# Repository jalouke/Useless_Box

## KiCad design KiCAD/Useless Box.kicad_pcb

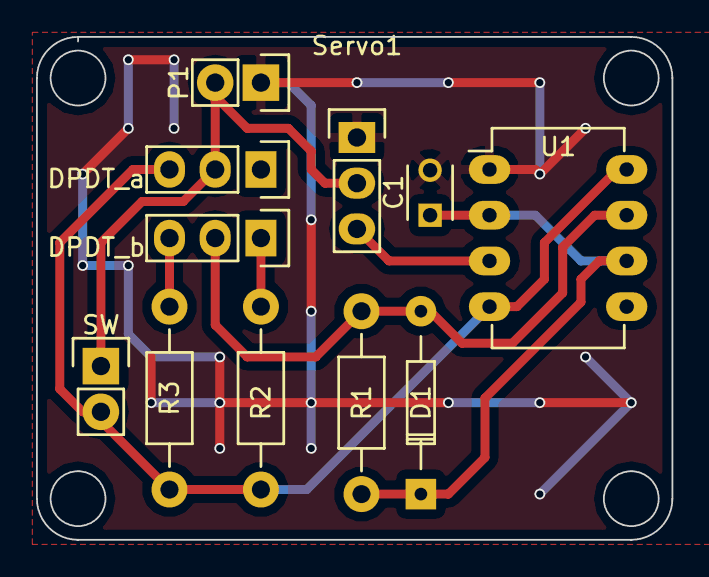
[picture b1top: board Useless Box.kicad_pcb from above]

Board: 2 copper layers, 35.3 x 27.9 mm, 11 parts (0 on the bottom side), 8 nets.

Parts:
C1: 0.1 uF; C_Disc_D3_P2.5
D1: 1N4004; Diode_DO-35_SOD27_Horizontal_RM10
DPDT_a: Switch_SPDT_x2; Pin_Header_Straight_1x03
DPDT_b: Pin_Header_Straight_1x03
P1: CONN_01X02; Pin_Header_Straight_1x02
R1: 220k; Resistor_Horizontal_RM10mm
R2: 27k; Resistor_Horizontal_RM10mm
R3: 15k; Resistor_Horizontal_RM10mm
SW: SPST; Pin_Header_Straight_1x02
Servo1: CONN_01X03; Pin_Header_Straight_1x03
U1: NE555; DIP-8_W7.62mm_LongPads

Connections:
+5V: DPDT_a.2, P1.2, SW.1, Servo1.2
GND: C1.2, P1.1, Servo1.1, U1.1
unnamed: C1.1, D1.1, R1.2, U1.2, U1.6
unnamed: D1.2, DPDT_b.2, R1.1, U1.7
unnamed: DPDT_a.3, R2.1, R3.1, SW.2, U1.4, U1.8
unnamed: DPDT_b.1, R2.2
unnamed: DPDT_b.3, R3.2
unnamed: Servo1.3, U1.3

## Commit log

2016-10-29 updated schematic and board layout, fixed mis-wiring of servo pins
2016-10-29 finished update
2016-10-29 adding CAD for box
